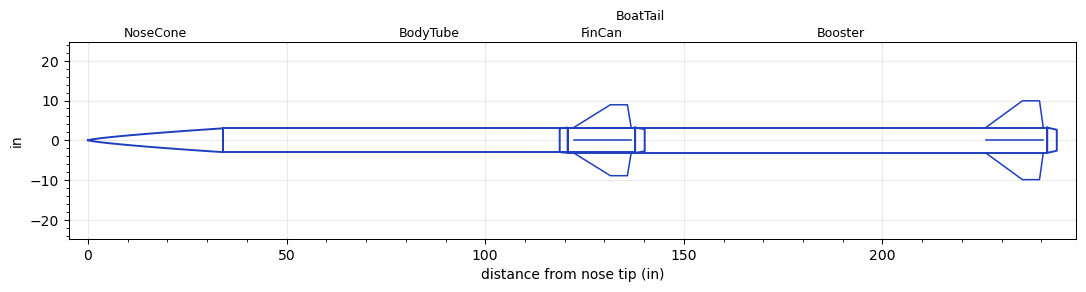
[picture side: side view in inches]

<RASAeroDocument>
 <FileVersion>2</FileVersion>
 <RocketDesign>
  <NoseCone>
   <Length>34</Length>
   <Diameter>6</Diameter>
   <Shape>Power Law</Shape>
   <BluntRadius>0.125</BluntRadius>
   <Location>0</Location>
   <PowerLaw>0.75</PowerLaw>
  </NoseCone>
  <BodyTube>
   <Length>103.75</Length>
   <Diameter>6</Diameter>
   <Location>34</Location>
  </BodyTube>
  <FinCan>
   <Length>17</Length>
   <Diameter>6.35</Diameter>
   <InsideDiameter>6</InsideDiameter>
   <Location>137.75</Location>
   <ShoulderLength>2</ShoulderLength>
   <Offset>-17</Offset>
   <Fin>
    <Count>4</Count>
    <Chord>14.5</Chord>
    <Span>5.75</Span>
    <SweepDistance>9.25</SweepDistance>
    <TipChord>4.3</TipChord>
    <Thickness>0.25</Thickness>
    <LERadius>0.08</LERadius>
    <Location>15.5</Location>
    <AirfoilSection>Hexagonal</AirfoilSection>
    <FX1>0.5</FX1>
    <FX3>0.5</FX3>
   </Fin>
  </FinCan>
  <BoatTail>
   <Length>2.4</Length>
   <Diameter>6.35</Diameter>
   <RearDiameter>5.6</RearDiameter>
   <Location>137.75</Location>
  </BoatTail>
  <Booster>
   <Length>103.75</Length>
   <Diameter>6.35</Diameter>
   <InsideDiameter>6.35</InsideDiameter>
   <Location>137.75</Location>
   <ShoulderLength>0</ShoulderLength>
   <BoattailLength>2.4</BoattailLength>
   <BoattailRearDiameter>5.3</BoattailRearDiameter>
   <Fin>
    <Count>4</Count>
    <Chord>14.5</Chord>
    <Span>6.75</Span>
    <SweepDistance>9.25</SweepDistance>
    <TipChord>4.3</TipChord>
    <Thickness>0.25</Thickness>
    <LERadius>0.08</LERadius>
    <Location>15.5</Location>
    <AirfoilSection>Hexagonal</AirfoilSection>
    <FX1>0.5</FX1>
    <FX3>0.5</FX3>
   </Fin>
  </Booster>
  <Surface>Cast Iron (Very Rough)</Surface>
  <ModifiedBarrowman>True</ModifiedBarrowman>
  <Turbulence>True</Turbulence>
  <UseBooster1>False</UseBooster1>
  <UseBooster2>False</UseBooster2>
 </RocketDesign>
 <LaunchSite>
  <Altitude>3000</Altitude>
  <Pressure>0</Pressure>
  <RodAngle>30</RodAngle>
  <RodLength>18</RodLength>
  <Temperature>85</Temperature>
  <WindSpeed>8</WindSpeed>
 </LaunchSite>
 <Recovery>
  <Altitude1>1000</Altitude1>
  <Altitude2>1000</Altitude2>
  <DeviceType1>None</DeviceType1>
  <DeviceType2>None</DeviceType2>
  <Event1>False</Event1>
  <Event2>False</Event2>
  <Size1>1</Size1>
  <Size2>1</Size2>
  <EventType1>None</EventType1>
  <EventType2>None</EventType2>
  <CD1>1.33</CD1>
  <CD2>1.33</CD2>
 </Recovery>
 <SimulationList>
  <Simulation>
   <SustainerEngine>Q10000  (Q10000)</SustainerEngine>
   <SustainerLaunchWt>162</SustainerLaunchWt>
   <SustainerNozzleDiameter>4.7</SustainerNozzleDiameter>
   <SustainerCG>80</SustainerCG>
   <SustainerIgnitionDelay>15</SustainerIgnitionDelay>
   <Booster1Engine>Q10000  (Q10000)</Booster1Engine>
   <Booster1LaunchWt>324</Booster1LaunchWt>
   <Booster1SeparationDelay>0</Booster1SeparationDelay>
   <Booster1IgnitionDelay>0</Booster1IgnitionDelay>
   <Booster1CG>160</Booster1CG>
   <IncludeBooster1>True</IncludeBooster1>
   <Booster2Delay>0</Booster2Delay>
   <IncludeBooster2>False</IncludeBooster2>
   <TimetoApogee>68.64604</TimetoApogee>
   <MaxAltitude>54305.97</MaxAltitude>
   <MaxVelocity>5536.931</MaxVelocity>
  </Simulation>
 </SimulationList>
</RASAeroDocument>
